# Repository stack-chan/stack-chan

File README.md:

# Stack-chan

[日本語](./README_ja.md)

Stack-chan is an open-source, JavaScript-driven, super-kawaii robot built with M5Stack.

This repository provides firmware with M5StackChan CoreS3 as its standard configuration, user applications called MODs, browser development tools, cases, and schematics.

- Video (with English subtitles): https://youtu.be/fZb_mF08xV0
- Official hashtag: [`#stackchan` | `#ｽﾀｯｸﾁｬﾝ` (JP)](https://twitter.com/search?q=%23stackchan%20OR%20%23%EF%BD%BD%EF%BE%80%EF%BD%AF%EF%BD%B8%EF%BE%81%EF%BD%AC%EF%BE%9D)

## Getting started

If this is your first Stack-chan, start with a preassembled M5StackChan and the browser tools.

### 1. Get an M5StackChan

The standard M5StackChan AI Desktop Robot (K151) package is enough to get started.
The joystick remote controller is optional.

- Worldwide: [M5Stack Official Store](https://shop.m5stack.com/products/stackchan-kawaii-co-created-open-source-ai-desktop-robot)
- Japan: [M5StackChan](https://ssci.to/11129)
- Japan: [M5StackChan with joystick remote controller](https://ssci.to/11131)

### 2. Flash the firmware

Connect M5StackChan to a computer with a data-capable USB cable, then open the [Web firmware installer](https://stack-chan.github.io/stack-chan/web/flash/) in Chrome or Edge.
Select "M5StackChan CoreS3" as the device.
You do not need to install the Moddable SDK or ESP-IDF.

> [!IMPORTANT]
> Flashing this repository's firmware replaces the factory firmware supplied by M5Stack.
> To restore it, follow the restore procedure in the [M5Stack product documentation](https://docs.m5stack.com/en/StackChan) and use M5Burner.

### 3. Try a MOD

Find published MODs and mini apps in the [MOD Gallery](https://stack-chan.github.io/stack-chan/web/mod-gallery/).
Choose a MOD, then run it in the simulator or install it on a device.
Block-based samples can be opened directly in the block editor and changed.

## Browser tools

Use the [Stack-chan browser tools](https://stack-chan.github.io/stack-chan/web/) to set up a device, change its preferences, and create MODs in a browser.

| Tool | Purpose |
| --- | --- |
| [Firmware installer](https://stack-chan.github.io/stack-chan/web/flash/) | Flash firmware to a supported M5Stack over USB |
| [Preferences](https://stack-chan.github.io/stack-chan/web/preference/) | Change Wi-Fi and device preferences over BLE |
| [MOD Gallery](https://stack-chan.github.io/stack-chan/web/mod-gallery/) | Find, try, and install published MODs |
| [Block editor](https://stack-chan.github.io/stack-chan/web/editor/) | Create MODs with Blockly and run them in the simulator or on a device |
| [Shape face editor](https://stack-chan.github.io/stack-chan/web/face-editor/) | Arrange eyes and a mouth to create a custom Face |
| [Simulator](https://stack-chan.github.io/stack-chan/web/simulator/) | Run MODs with the WebAssembly firmware and a 3D model |
| [MediaPipe BLE tracking](https://stack-chan.github.io/stack-chan/web/mediapipe/) | Send tracked face and hand movement over BLE |
| [Usage & AI integration](https://stack-chan.github.io/stack-chan/web/guide/) | Read task guides and example requests for WebMCP agents |

WebMCP-capable browsers let agents edit blocks, faces, and robot preferences. See [WebMCP](./web/WEBMCP.md) for the tool contract and developer testing instructions.

## Supported hardware

The distributed firmware supports M5Stack, M5Stack Core2, M5Stack CoreS3, and M5StackChan CoreS3.
M5StackChan CoreS3 is the standard configuration and the target used for physical-device release validation.

Firmware for Stack-chan RT and Takao Core2 + SG90 can be built from source.
See the [firmware guide](./firmware/README.md) for target-specific commands and constraints.

To build the hardware yourself, see the [case guide](./case/README.md) for parts and assembly instructions.
See the [schematics](./schematics/README.md) for board information.

## Repository contents

- [firmware](./firmware/): Host firmware, modules, MODs, and development scripts
- [web](./web/): Firmware installer, preferences, editors, Gallery, and simulator
- [case](./case/): Case models for 3D printing
- [schematics](./schematics/): Schematics and board layouts
- [docs](./docs/): Roadmap, specifications, operations guides, and release notes

## Development

- [Firmware development](./firmware/README.md)
- [MOD development](./firmware/mods/README.md)
- [Firmware API](./firmware/docs/api.md)
- [Contribution guide](./CONTRIBUTING.md)
- [Latest release](https://github.com/stack-chan/stack-chan/releases/latest)
- [Development roadmap](./docs/ROADMAP.md)

## Contributing

Feature requests, bug reports, and pull requests are welcome.
Read the [contribution guide](./CONTRIBUTING.md), or open an [issue](https://github.com/stack-chan/stack-chan/issues).

To support the project financially, visit the [GitHub Sponsors page](https://github.com/sponsors/meganetaaan/).

## License

The resources in this repository are distributed under the Apache License 2.0.
See [LICENSE](./LICENSE).

## BibTeX

```bibtex
@misc{stackchan,
  author       = {Shinya Ishikawa and the Stack-chan community},
  title        = {Stack-chan: A JavaScript-driven Super-kawaii Robot},
  year         = {2021},
  howpublished = {\url{https://github.com/stack-chan/stack-chan}},
  note         = {Open-source hardware and software.},
}
```

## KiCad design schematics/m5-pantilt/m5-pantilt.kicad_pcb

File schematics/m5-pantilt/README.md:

# Stack-chan schematics

TOP

BOTTOM

## Feature

* Drive two servos
  * TTL or
  * PWM * 2ch
* M5Unit port
  * PortB
  * PortC(only available with PWM servo)
* Battery
* (Optional) Power switch

## Parts

|Reference| Quantity| Value| Footprint| URL|
|:--:|:--|:--|:--|:--|
| C1 |1|"100u"|"Capacitor_THT:C_Radial_D6.3mm_H11.0mm_P2.50mm"|"https://www.sengoku.co.jp/mod/sgk_cart/detail.php?code=46S8-5GL7"|
| J1 |1|"Conn_02x15_Odd_Even"|"Connector_PinHeader_2.54mm:PinHeader_2x15_P2.54mm_Vertical_SMD"|"https://www.switch-science.com/catalog/3654/"|
| J2 J3 |2|"Conn_02x03_Odd_Even"|"Connector_PinHeader_2.54mm:PinHeader_2x03_P2.54mm_Vertical"||
| J5 |1|"BAT"|"Connector_JST:JST_PH_B2B-PH-K_1x02_P2.00mm_Vertical"|"https://akizukidenshi.com/catalog/g/gC-12802/"|
| J4 J6 |2|"Conn_01x04"|"Connector_JST:JST_PH_S4B-PH-K_1x04_P2.00mm_Horizontal"||
| JP1 JP2 |2|"Jumper_3_Bridged12"|"Jumper:SolderJumper-3_P1.3mm_Bridged12_RoundedPad1.0x1.5mm"||
| R1 R3 R4 |3|"1k"|"Resistor_SMD:R_0603_1608Metric_Pad1.05x0.95mm_HandSolder"||
| R2 |1|"100"|"Resistor_SMD:R_0603_1608Metric_Pad1.05x0.95mm_HandSolder"|"https://www.sengoku.co.jp/mod/sgk_cart/detail.php?code=EEHD-57FV"|
| SW1 |1|"SW_SPDT"|"Button_Switch_THT:SW_E-Switch_EG1224_SPDT_Angled"||
| U1 |1|"NL27WZ125"|"NL27WZ125USG"|"https://www.digikey.jp/number/ja/on-semiconductor/488/NL27WZ125/291486"|

## Assembly

TODO

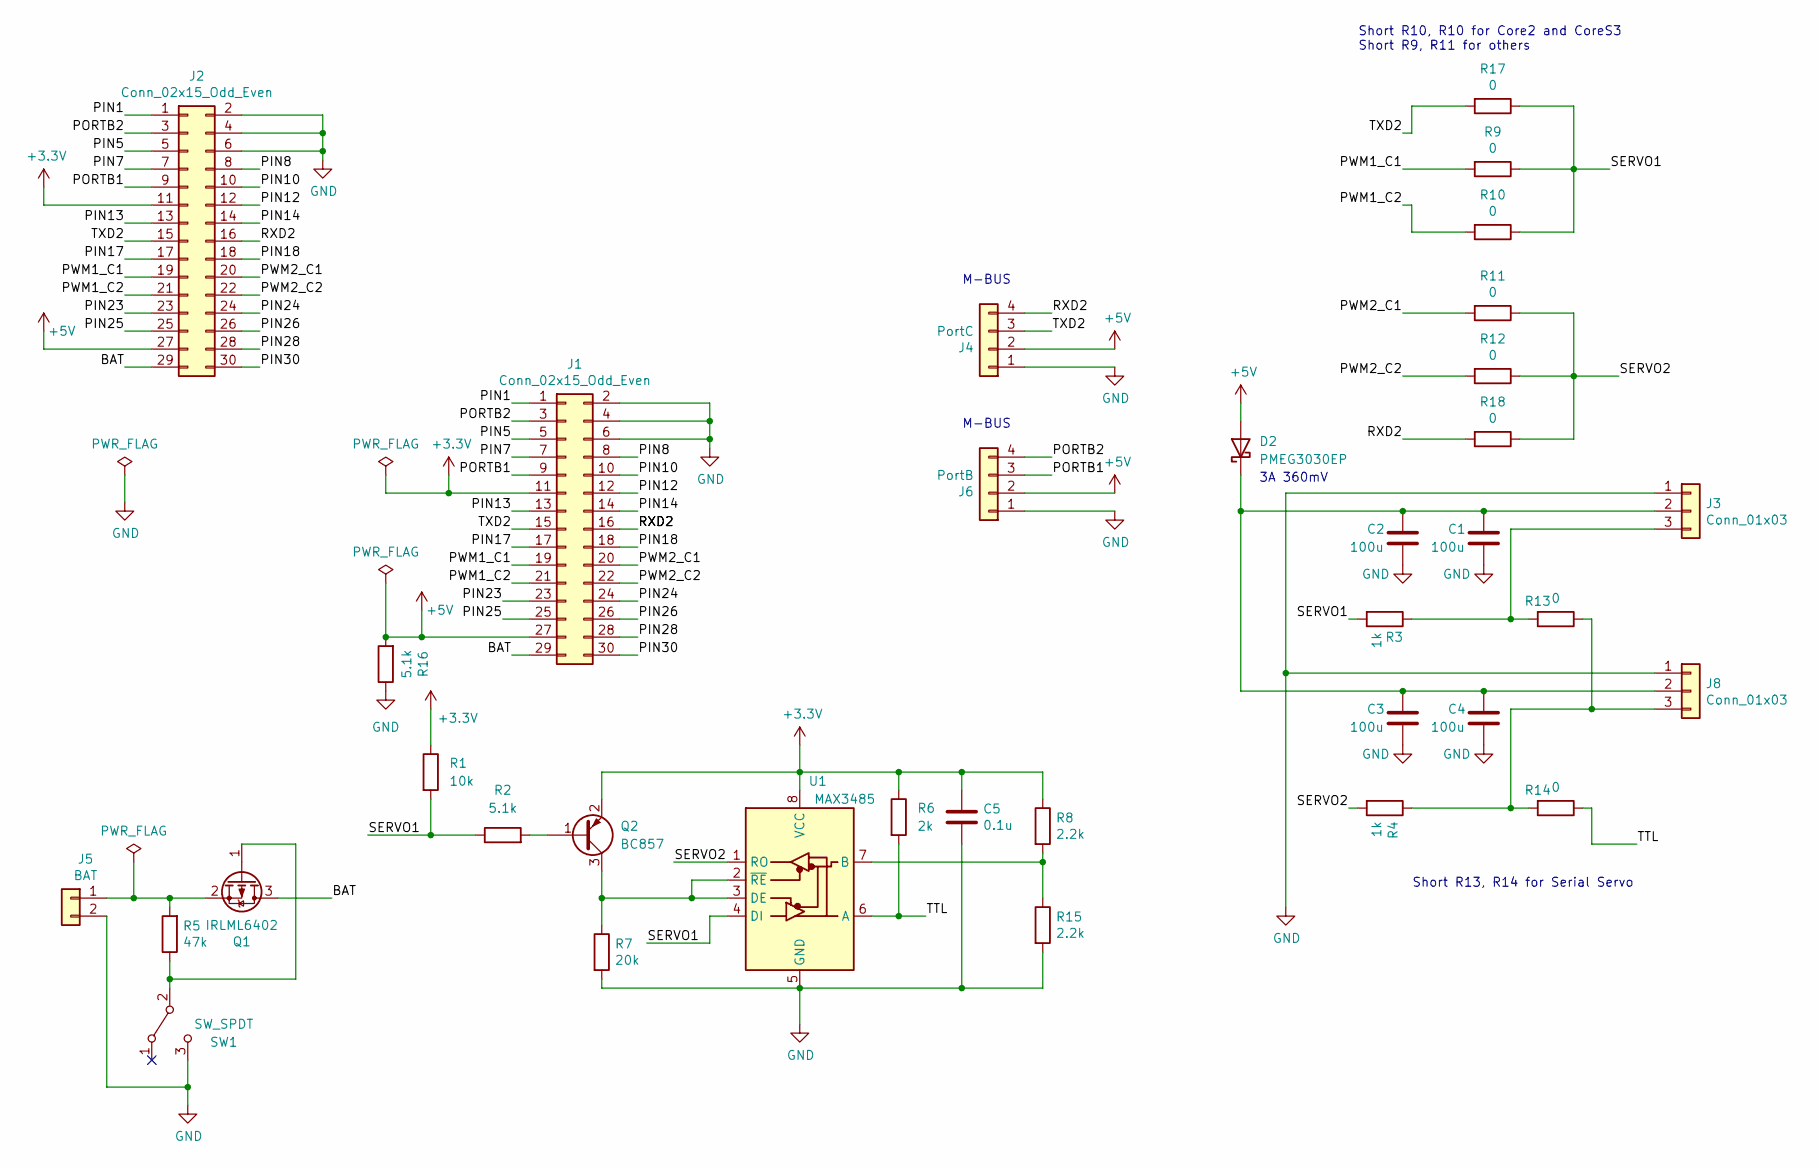
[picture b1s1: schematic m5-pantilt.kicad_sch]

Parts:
C1, C2, C3, C4: 100u; C_1206_3216Metric_Pad1.33x1.80mm_HandSolder; LCSC C15008
C5: 0.1u; C_0603_1608Metric; LCSC C14663
D2: PMEG3030EP; D_SOD-128; LCSC C255587
J1: Conn_02x15_Odd_Even; PinHeader_2x15_P2.54mm_Vertical_SMD
J2: Conn_02x15_Odd_Even; PinSocket_2x15_P2.54mm_Vertical_SMD
J3, J8: Conn_01x03; JST_EH_B3B-EH-A_1x03_P2.50mm_Vertical
J4: PortC; JST_PH_S4B-PH-K_1x04_P2.00mm_Horizontal
J5: BAT; JST_PH_B2B-PH-K_1x02_P2.00mm_Vertical; LCSC C2319
J6: PortB; JST_PH_S4B-PH-K_1x04_P2.00mm_Horizontal
Q1: IRLML6402; SOT-23; LCSC C2886430
Q2: BC857; SOT-23; LCSC C2139
R1: 10k; R_0603_1608Metric; LCSC C25804
R2: 5.1k; R_0603_1608Metric; LCSC C23186
R3, R4: 1k; R_0603_1608Metric_Pad0.98x0.95mm_HandSolder; LCSC C21190
R5: 47k; R_0603_1608Metric_Pad0.98x0.95mm_HandSolder; LCSC C25819
R6: 2k; R_0603_1608Metric; LCSC C22975
R7: 20k; R_0603_1608Metric; LCSC C4184
R8, R15: 2.2k; R_0603_1608Metric; LCSC C4190
R9, R10, R11, R12, R17, R18: 0; R_0603_1608Metric_Pad0.98x0.95mm_HandSolder; LCSC C21189
R13, R14: 0; R_0603_1608Metric; LCSC C21189
R16: 5.1k; R_0603_1608Metric_Pad0.98x0.95mm_HandSolder; LCSC C21189
SW1: SW_SPDT; SW_CuK_OS102011MA1QN1_SPDT_Angled
U1: MAX3485; SO-8_5.3x6.2mm_P1.27mm; LCSC C668204

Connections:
+3V3: C5.1, J1.11, J2.11, Q2.2 (E), R1.1, R6.1, R8.1, U1.8 (VCC)
+5V: D2.2 (A), J1.27, J2.27, J4.2, J6.2, R16.2
/BAT: J1.29, J2.29, Q1.3 (D)
/PIN1: J1.1, J2.1
/PIN5: J1.5, J2.5
/PIN7: J1.7, J2.7
/PIN8: J1.8, J2.8
/PIN10: J1.10, J2.10
/PIN12: J1.12, J2.12
/PIN13: J1.13, J2.13
/PIN14: J1.14, J2.14
/PIN17: J1.17, J2.17
/PIN18: J1.18, J2.18
/PIN23: J1.23, J2.23
/PIN24: J1.24, J2.24
/PIN25: J1.25, J2.25
/PIN26: J1.26, J2.26
/PIN28: J1.28, J2.28
/PIN30: J1.30, J2.30
/PORTB1: J1.9, J2.9, J6.3
/PORTB2: J1.3, J2.3, J6.4
/PWM1_C1: J1.19, J2.19, R9.2
/PWM1_C2: J1.21, J2.21, R10.2
/PWM2_C1: J1.20, J2.20, R11.2
/PWM2_C2: J1.22, J2.22, R12.2
/RXD2: J1.16, J2.16, J4.4, R18.2
/SERVO1: R1.2, R2.1, R3.2, R9.1, R10.1, R17.1, U1.4 (DI)
/SERVO2: R4.2, R11.1, R12.1, R18.1, U1.1 (RO)
/TTL: R6.2, R14.1, U1.6 (A)
/TXD2: J1.15, J2.15, J4.3, R17.2
GND: C1.1, C2.1, C3.2, C4.1, C5.2, J1.2, J1.4, J1.6, J2.2, J2.4, J2.6, J3.1, J4.1, J5.2, J6.1, J8.1, R7.2, R15.2, R16.1, SW1.3 (C), U1.5 (GND)
unnamed: C1.2, C2.2, C3.1, C4.2, D2.1 (K), J3.2, J8.2
unnamed: J3.3, R3.1, R13.2
unnamed: J5.1, Q1.2 (S), R5.2
unnamed: J8.3, R4.1, R13.1, R14.2
unnamed: Q1.1 (G), R5.1, SW1.2 (B)
unnamed: Q2.1 (B), R2.2
unnamed: Q2.3 (C), R7.1, U1.2 (~RE), U1.3 (DE)
unnamed: R8.2, R15.1, U1.7 (B)

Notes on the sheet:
M-BUS
Short R13, R14 for Serial Servo
3A 360mV
Short R10, R10 for Core2 and CoreS3 Short R9, R11 for others

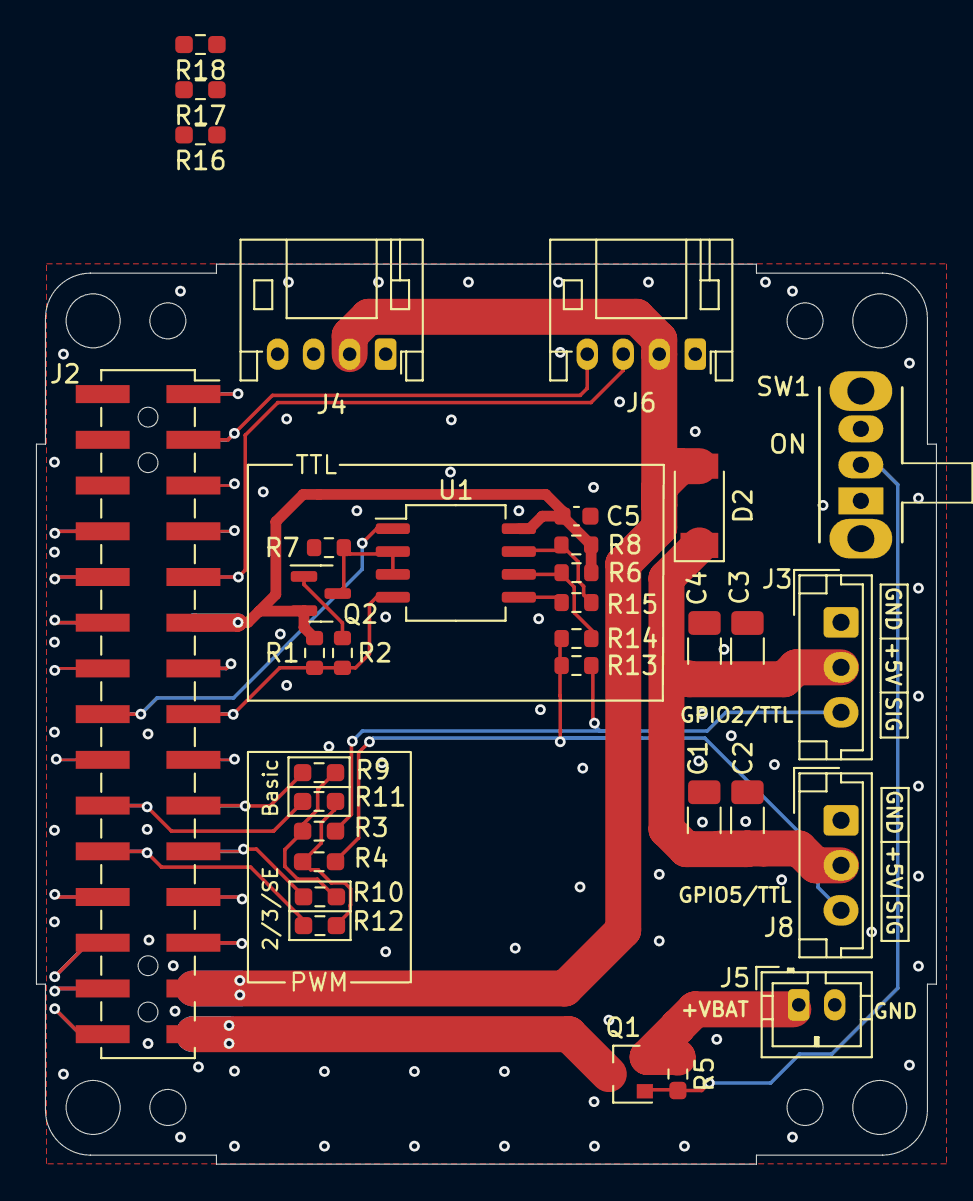
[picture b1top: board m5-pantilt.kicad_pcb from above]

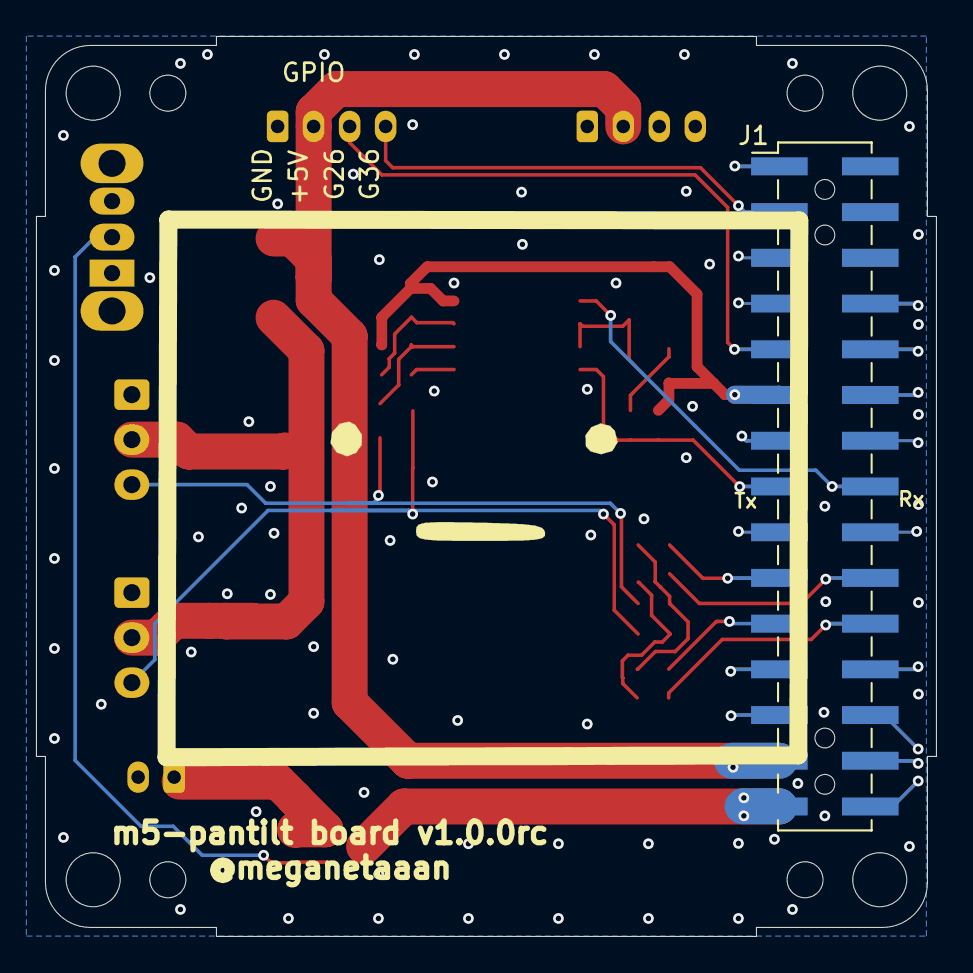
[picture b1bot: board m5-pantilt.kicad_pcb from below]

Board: 2 copper layers, 50.0 x 50.0 mm, 40 parts (2 on the bottom side), 39 nets.

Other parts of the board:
Hole1, Hole2, Hole3, Hole4: mountinghole_M2_M3
LOGO: LOGO; avatar_small
